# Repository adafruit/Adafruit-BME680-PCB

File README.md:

## Adafruit BME680 PCB

<a href="http://www.adafruit.com/products/3660"><br/>
Click here to purchase one from the Adafruit shop</a>

PCB files for the Adafruit BME680 Breakout. Format is EagleCAD schematic and board layout

For more details, check out the product page at
* https://www.adafruit.com/product/3660

### Description

The long awaited BME680 from Bosch gives you all the environmental sensing you want in one small package. This little sensor contains temperature, humidity, barometric pressure, and VOC gas sensing capabilities. All over SPI or I2C at a great price!

Like the BME280 & BMP280, this precision sensor from Bosch can measure humidity with ±3% accuracy, barometric pressure with ±1 hPa absolute accuracy, and temperature with ±1.0°C accuracy. Because pressure changes with altitude, and the pressure measurements are so good, you can also use it as an altimeter with  ±1 meter or better accuracy!

The BME680 takes those sensors to the next step in that it contains a small MOX sensor. The heated metal oxide changes resistance based on the volatile organic compounds (VOC) in the air, so it can be used to detect gasses & alcohols such as Ethanol, Alcohol and Carbon Monoxide, and perform air quality measurements. Note it will give you one resistance value, with overall VOC content, but it cannot differentiate gasses or alcohols.

Please note this sensor, like all VOC/gas sensors, has variability and to get precise measurements you will want to calibrate it against known sources! That said, for general environmental sensors, it will give you a good idea of trends and comparisons. We recommend that you run this sensor for 48 hours when you first receive it to "burn it in", and then 30 minutes in the desired mode every time the sensor is in use. This is because the sensitivity levels of the sensor will change during early use, and the resistance will slowly rise over time as the MOX warms up to its baseline reading.

For your convenience we've pick-and-placed the sensor on a PCB with a 3.3V regulator and some level shifting, so it can be easily used with your favorite 3.3V or 5V microcontroller.

### License

Adafruit invests time and resources providing this open source design, please support Adafruit and open-source hardware by purchasing products from [Adafruit](https://www.adafruit.com)!

Designed by Limor Fried/Ladyada for Adafruit Industries.

Creative Commons Attribution/Share-Alike, all text above must be included in any redistribution. See license.txt for additional details.

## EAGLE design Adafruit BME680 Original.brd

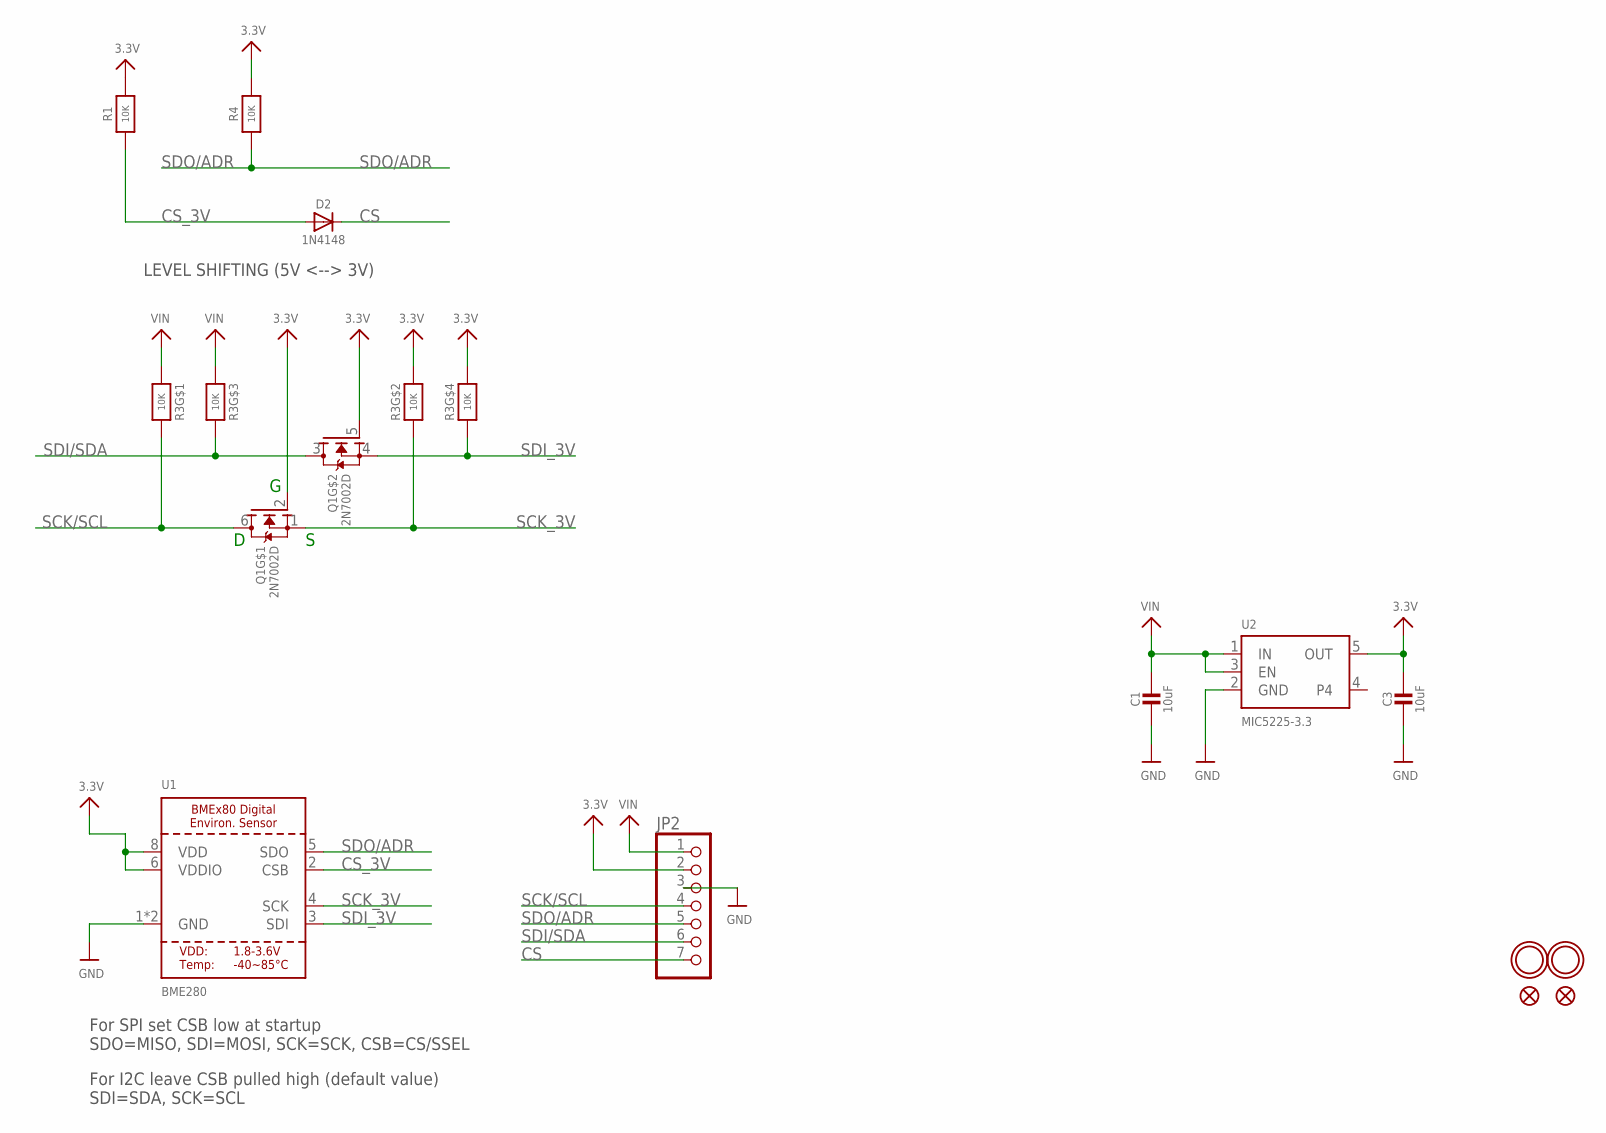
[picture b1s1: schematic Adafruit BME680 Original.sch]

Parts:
C1, C3: 10uF; 0805-NO
D2: 1N4148; SOD-323
JP2: HEADER-1X770MIL; 1X07_ROUND_70
Q1: 2N7002D; SOT363
R1, R4: 10K; 0603-NO
R3: 10K; RESPACK_4X0603
U1: BME280; BME680
U2: MIC5225-3.3; SOT23-5
U$5, U$15: FIDUCIAL_1MM
U$7, U$8: MOUNTINGHOLE2.0; MOUNTINGHOLE_2.0_PLATED

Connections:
3.3V: C3.1, JP2.2, Q1.2 (G), Q1.5 (G), R1.2, R3.2 (1), R3.4 (1), R4.2, U1.6 (VDDIO), U1.8 (VDD), U2.5 (OUT)
CS: D2.C, JP2.7
CS_3V: D2.A, R1.1, U1.2 (CSB)
GND: C1.2, C3.2, JP2.3, U1.1 (GND), U1.7 (GND), U2.2 (GND)
SCK/SCL: JP2.4, Q1.6 (D), R3.8 (2)
SCK_3V: Q1.1 (S), R3.7 (2), U1.4 (SCK)
SDI/SDA: JP2.6, Q1.3 (D), R3.6 (2)
SDI_3V: Q1.4 (S), R3.5 (2), U1.3 (SDI)
SDO/ADR: JP2.5, R4.1, U1.5 (SDO)
VIN: C1.1, JP2.1, R3.1, R3.3 (1), U2.1 (IN), U2.3 (EN)

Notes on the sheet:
For SPI set CSB low at startup SDO=MISO, SDI=MOSI, SCK=SCK, CSB=CS/SSEL
For I2C leave CSB pulled high (default value) SDI=SDA, SCK=SCL
LEVEL SHIFTING (5V <--> 3V)

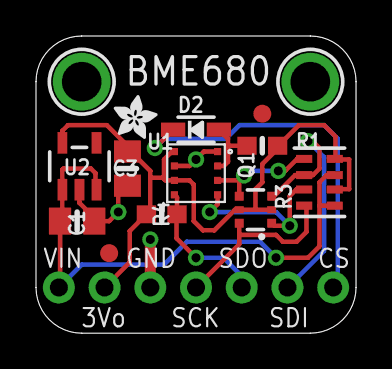
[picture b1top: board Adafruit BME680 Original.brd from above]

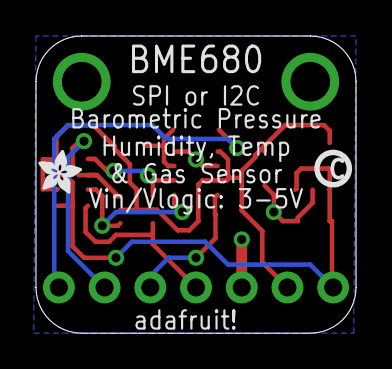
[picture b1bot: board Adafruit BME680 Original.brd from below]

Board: 2 copper layers, 17.8 x 16.5 mm, 17 parts (2 on the bottom side), 10 nets.

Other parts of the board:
U$2, U$6: ADAFRUIT_2.5MM
U$20: PCBFEAT-REV-040

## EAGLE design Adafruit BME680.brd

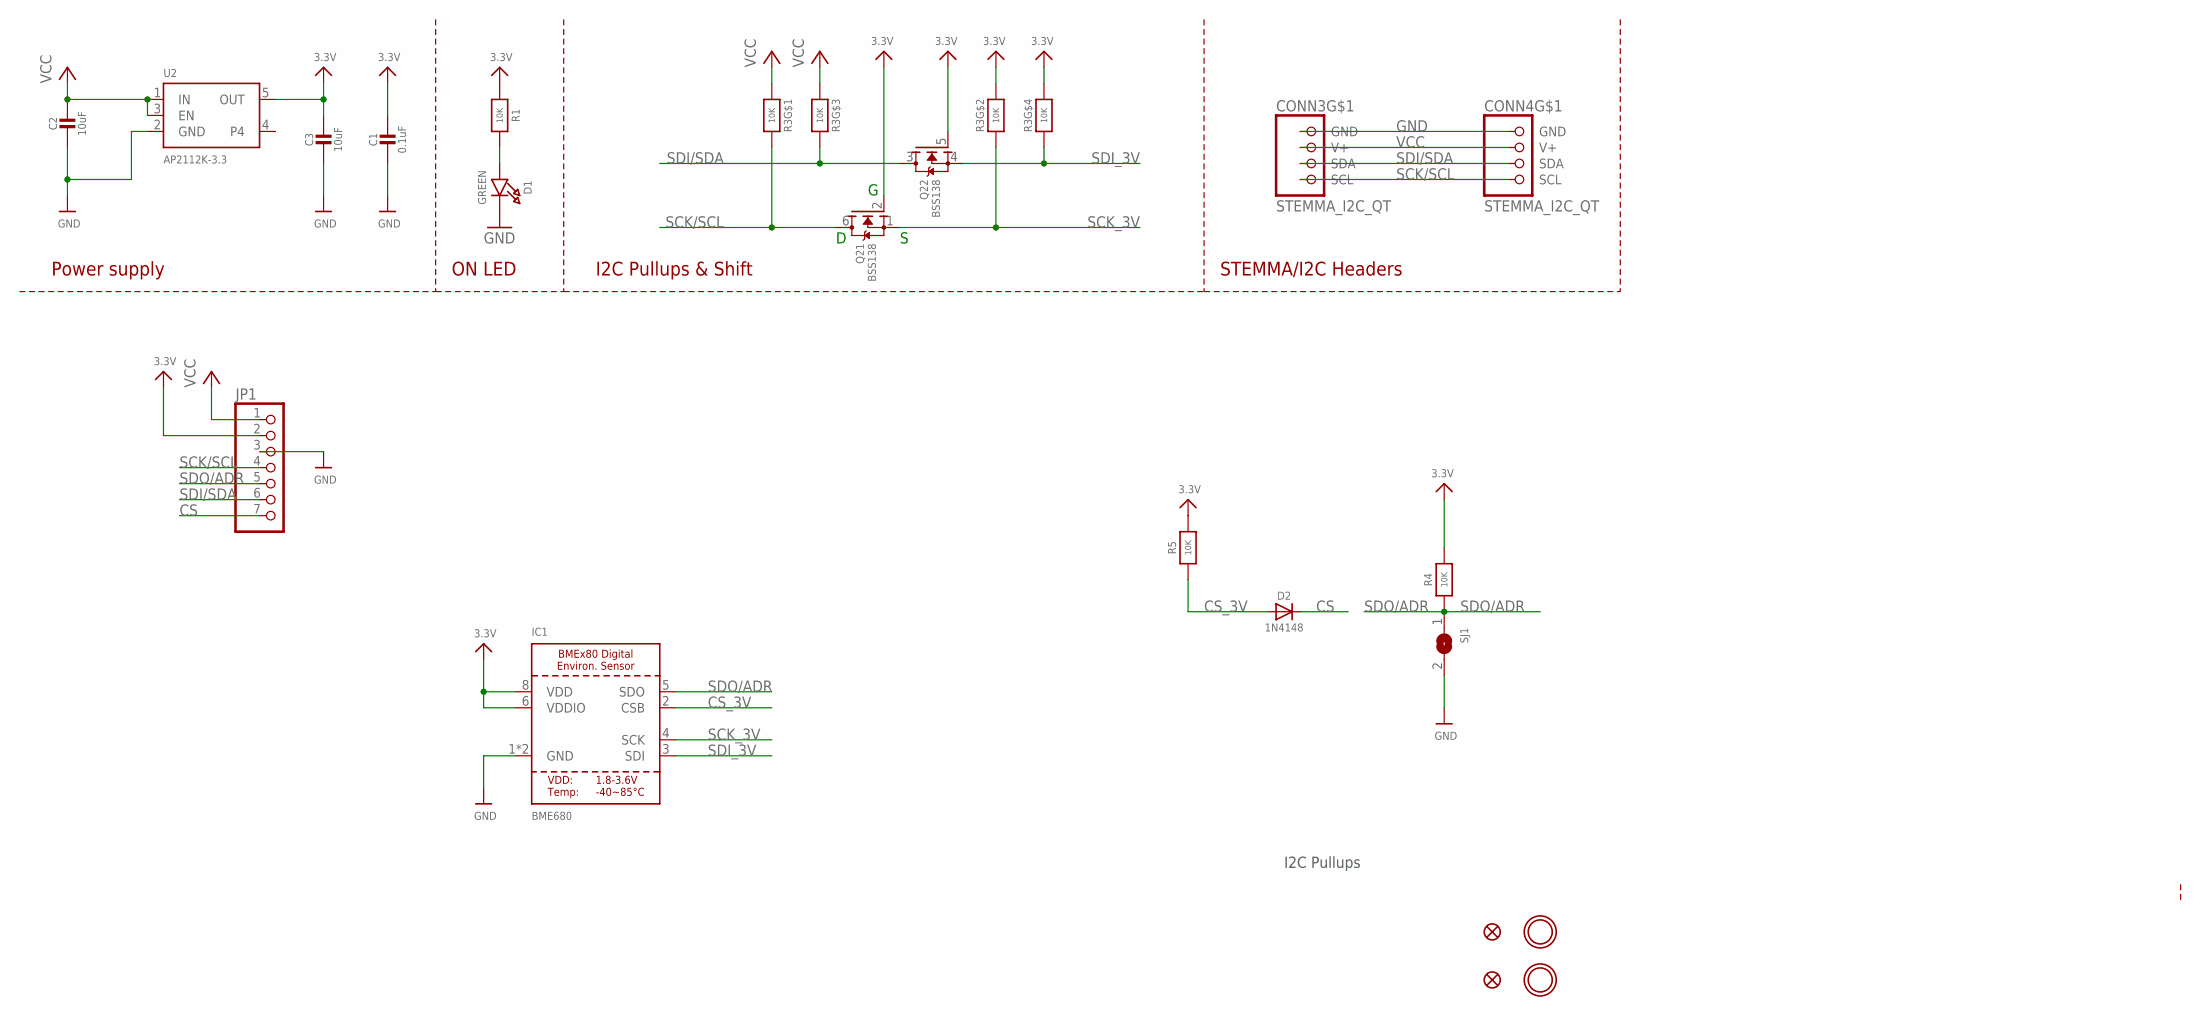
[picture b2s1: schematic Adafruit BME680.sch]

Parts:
C1: 0.1uF; 0603-NO
C2, C3: 10uF; 0805-NO
CONN3, CONN4: STEMMA_I2C_QT; JST_SH4
D1: GREEN; CHIPLED_0603_NOOUTLINE
D2: 1N4148; SOD-323
FID3, FID4: FIDUCIAL_1MM
IC1: BME680
JP1: HEADER-1X770MIL; 1X07_ROUND_70
Q2: BSS138; SOT363
R1, R4, R5: 10K; 0603-NO
R3: 10K; RESPACK_4X0603
SJ1: SOLDERJUMPER; SOLDERJUMPER_ARROW_NOPASTE
U2: AP2112K-3.3; SOT23-5
U$1, U$17: MOUNTINGHOLE2.5; MOUNTINGHOLE_2.5_PLATED

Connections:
3.3V: C1.1, C3.1, IC1.6 (VDDIO), IC1.8 (VDD), JP1.2, Q2.2 (G), Q2.5 (G), R1.1, R3.2 (1), R3.4 (1), R4.2, R5.2, U2.5 (OUT)
CS: D2.C, JP1.7
CS_3V: D2.A, IC1.2 (CSB), R5.1
GND: C1.2, C2.2, C3.2, CONN3.1 (GND), CONN4.1 (GND), D1.C, IC1.1 (GND), IC1.7 (GND), JP1.3, SJ1.2, U2.2 (GND)
unnamed: D1.A, R1.2
SCK/SCL: CONN3.4 (SCL), CONN4.4 (SCL), JP1.4, Q2.6 (D), R3.8 (2)
SCK_3V: IC1.4 (SCK), Q2.1 (S), R3.7 (2)
SDI/SDA: CONN3.3 (SDA), CONN4.3 (SDA), JP1.6, Q2.3 (D), R3.6 (2)
SDI_3V: IC1.3 (SDI), Q2.4 (S), R3.5 (2)
SDO/ADR: IC1.5 (SDO), JP1.5, R4.1, SJ1.1
VCC: C2.1, CONN3.2 (V+), CONN4.2 (V+), JP1.1, R3.1, R3.3 (1), U2.1 (IN), U2.3 (EN)

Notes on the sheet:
I2C Pullups & Shift
STEMMA/I2C Headers
ON LED
Power supply
I2C Pullups

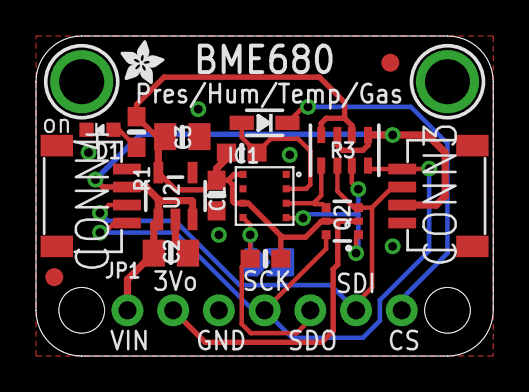
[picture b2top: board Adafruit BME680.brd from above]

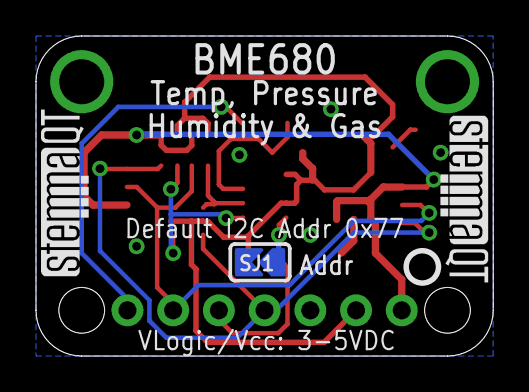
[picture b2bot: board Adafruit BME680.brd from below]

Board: 2 copper layers, 25.4 x 17.8 mm, 24 parts (4 on the bottom side), 11 nets.

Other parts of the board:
U$4: ADAFRUIT_2.5MM
U$25: PCBFEAT-REV-040
U$30, U$31: STEMMAQT

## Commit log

2017-11-08 init
2022-01-28 Updated PCB files
2022-02-08 Readd original board files.

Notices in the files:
parts and their libraries:
microbuilder: This work is placed in the public domain, and may be freely used for commercial and non-commercial work with the following conditions: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
